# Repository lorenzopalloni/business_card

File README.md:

# Naive Business Card
In my journey of learning Electronics and PCB design, and with the philosophy "fail fast, fail often" in mind, I wanted to challenge myself with the [Hackaday 2024 Business Card Contest](https://hackaday.io/contest/195949-2024-business-card-contest). I created a very simple business card with a couple of LEDs whose blinking frequency can be adjusted by a trimmer.

I used KiCad 8.0.

https://github.com/user-attachments/assets/3243e91c-fb37-439d-8b24-2ccace285e78

## Demo
<video controls src="log/2024_07_15/naive-business-card_demo_compressed.mp4" title="Demo: Naive Business Card"></video>

## Acknowledgement
Among others, I want to thank Shawn Hymel, Philip Salmony (Phil's Lab), and Charles Platt, from whom I have learnt a ton.

- KiCad Tutorial, by Shawn Hymel: https://www.youtube.com/playlist?list=PL3bNyZYHcRSUhUXUt51W6nKvxx2ORvUQB

- KiCad 7 STM32 Bluetooth Hardware Design (1/2 Schematic), by Phil's Lab: https://www.youtube.com/watch?v=nkHFoxe0mrU

- Make: Electronics, by Charles Platt: https://www.amazon.it/Make-Electronics-Learning-Through-Discovery/dp/0596153740

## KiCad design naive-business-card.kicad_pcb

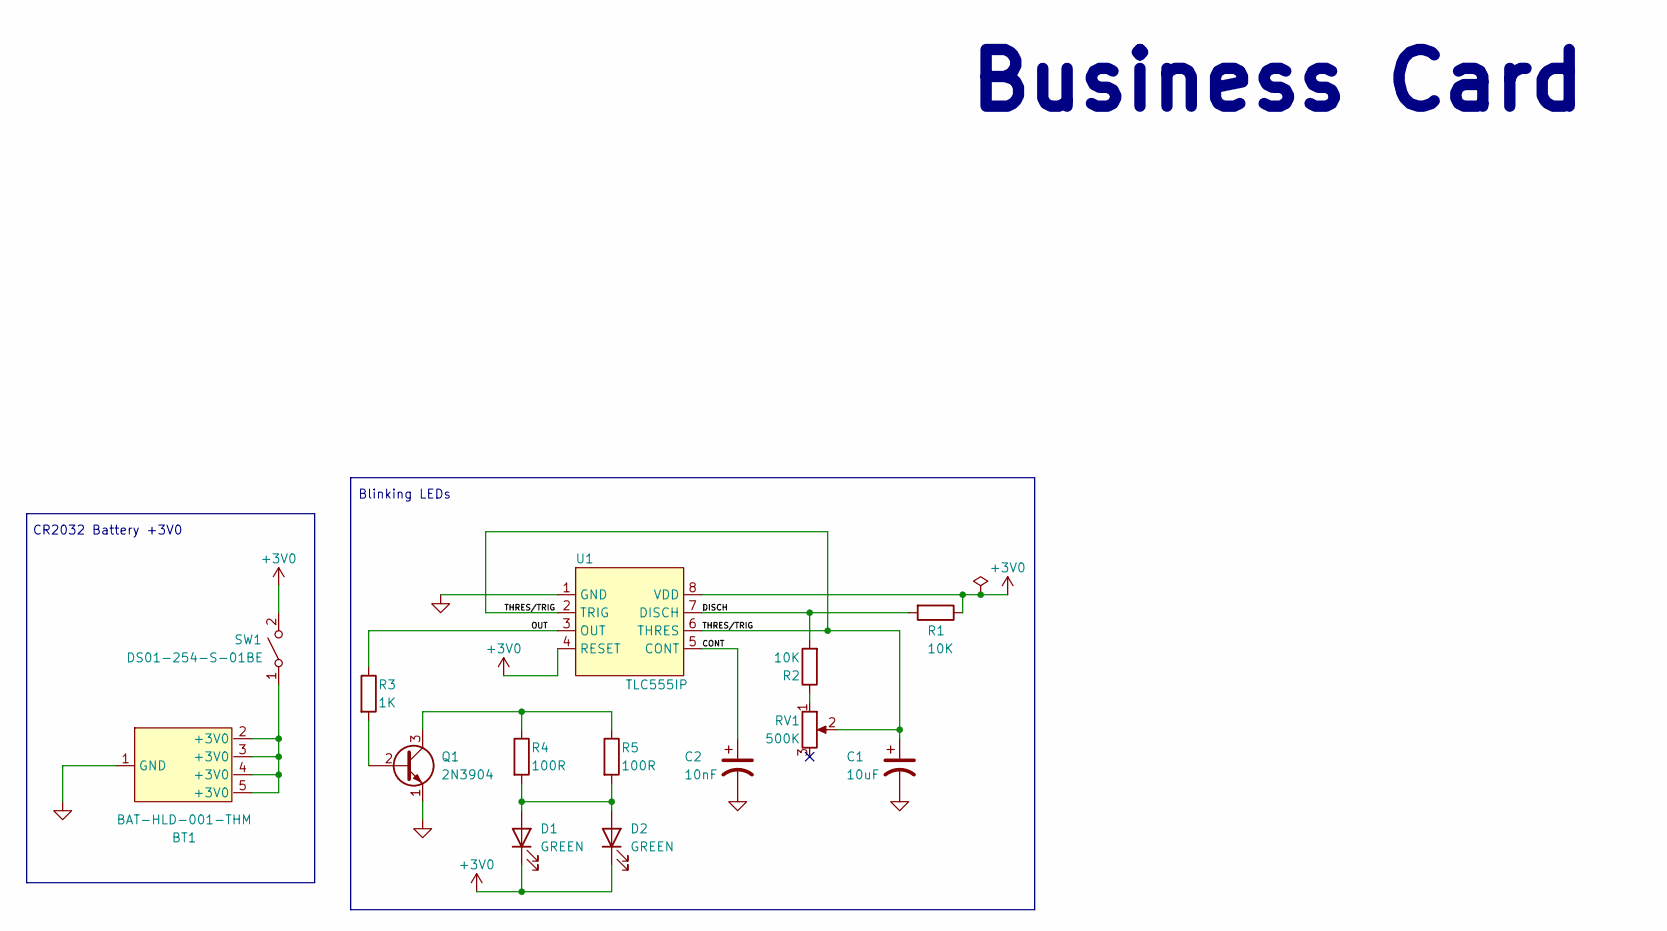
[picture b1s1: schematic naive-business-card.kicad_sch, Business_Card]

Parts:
BT1: BAT-HLD-001-THM
C1: 10uF; CP_Radial_D4.0mm_P2.00mm
C2: 10nF; CP_Radial_Tantal_D6.0mm_P5.00mm
D1, D2: GREEN; LED_D3.0mm
Q1: 2N3904
R1, R2: 10K; R_Axial_DIN0207_L6.3mm_D2.5mm_P10.16mm_Horizontal
R3: 1K; R_Axial_DIN0207_L6.3mm_D2.5mm_P10.16mm_Horizontal
R4, R5: 100R; R_Axial_DIN0207_L6.3mm_D2.5mm_P10.16mm_Horizontal
RV1: 500K; 3306P-1-504
SW1: DS01-254-S-01BE
U1: TLC555IP

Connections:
+3V0: D1.1 (K), D2.1 (K), R1.1, SW1.2, U1.4 (RESET), U1.8 (VDD)
/CONT: C2.1, U1.5 (CONT)
/DISCH: R1.2, R2.2, U1.7 (DISCH)
/OUT: R3.1, U1.3 (OUT)
/THRES/TRIG: C1.1, RV1.2, U1.2 (TRIG), U1.6 (THRES)
GND: BT1.1 (GND), C1.2, C2.2, Q1.1 (E), U1.1 (GND)
unnamed: BT1.2 (+3V0), BT1.3 (+3V0), BT1.4 (+3V0), BT1.5 (+3V0), SW1.1
unnamed: D1.2 (A), D2.2 (A), R4.2, R5.2
unnamed: Q1.2 (B), R3.2
unnamed: Q1.3 (C), R4.1, R5.1
unnamed: R2.1, RV1.1

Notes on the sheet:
Business Card
CR2032 Battery +3V0
Blinking LEDs

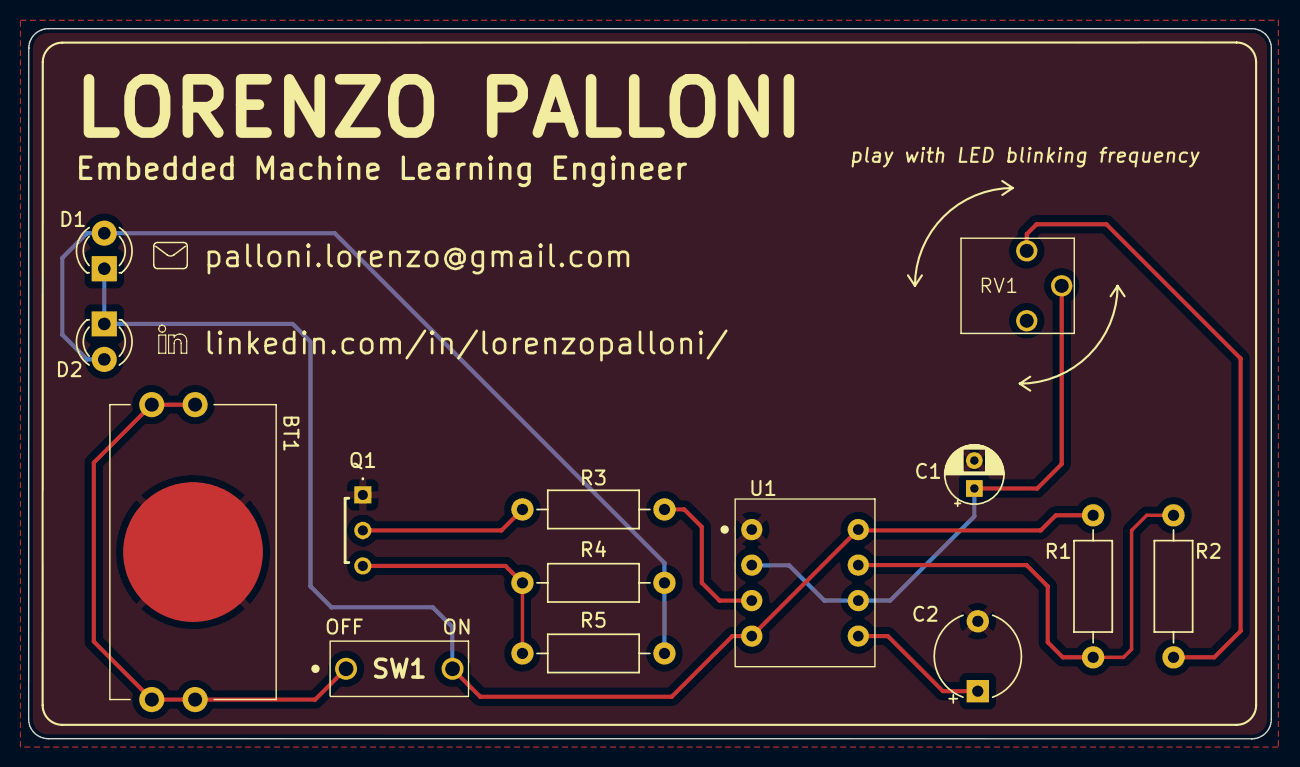
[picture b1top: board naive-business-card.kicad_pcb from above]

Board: 2 copper layers, 88.9 x 50.8 mm, 14 parts (0 on the bottom side), 11 nets.

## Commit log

2024-05-31 Add schematic and footprints
2024-06-04 Add battery holder schematic, footprint and 3d model
2024-06-04 Add battery holder's datasheet
2024-06-04 Add SPST switch
2024-06-16 Add potentiometer and update switch footprint
2024-06-17 Add configurations to start connecting components
2024-06-19 Set KiCad Board Setup
2024-06-19 Add battery holder footprint
2024-06-19 Fix bug on battery holder footprint
2024-06-20 Update PCB layout
2024-06-22 Add traces and Replace 2N3904 footprint
2024-06-29 Add license and 2n3904 3d model
2024-06-29 Make the board ready for manufacturing! :)
2024-07-15 Rename repo
2024-07-15 Add compressed demo
2024-07-22 Rename the repo

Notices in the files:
naive-business-card.kicad_pcb:
License: MIT
